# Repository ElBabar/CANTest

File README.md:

# CANTest

A board designed to test CAN connectivity between 2 arduino nanos

The CAN bus is made using mcp2551 and mcp2515.

LEDs were placed to monitor SPI and CAN activity for debug purposes. A new, cleaner version is being designed (see TXDemo).

This designed was intended simple on a single faced PCB in order to produce it with tools I had under hand.

You might need to use my library:
add https://github.com/ElBabar/Libabar.git
to your KiCad paths.

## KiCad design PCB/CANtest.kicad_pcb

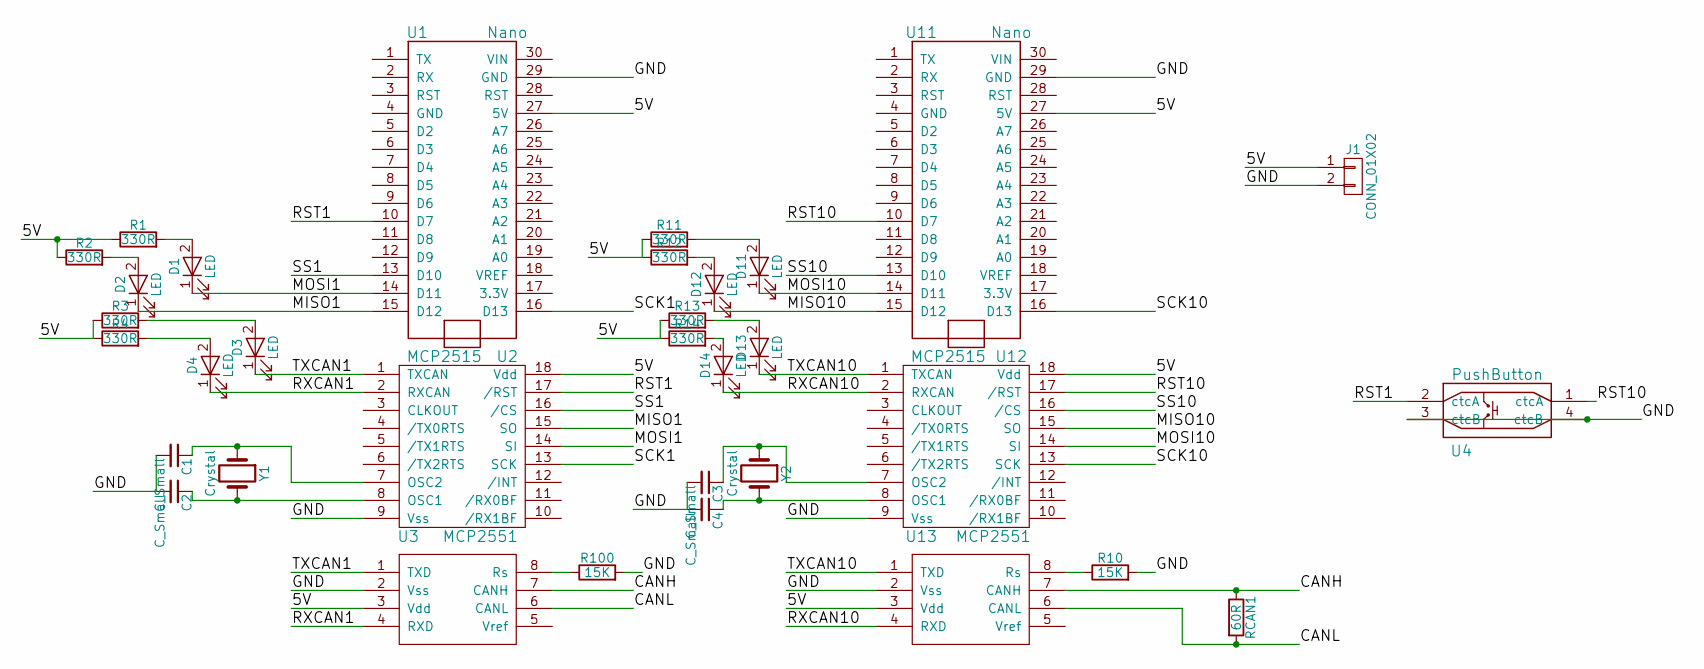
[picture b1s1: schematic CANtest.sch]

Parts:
C1, C2, C3, C4: C_Small; C_Disc_D3.0mm_W1.6mm_P2.50mm
D1, D2, D3, D4, D11, D12, D13, D14: LED; LED_D5.0mm
J1: CONN_01X02; Molex_KK-6410-02_02x2.54mm_Straight
R1, R2, R3, R4, R11, R12, R13, R14: 330R; R_Axial_DIN0207_L6.3mm_D2.5mm_P7.62mm_Horizontal
R10, R100: 15K; R_Axial_DIN0207_L6.3mm_D2.5mm_P10.16mm_Horizontal
RCAN1: 60R; R_Axial_DIN0207_L6.3mm_D2.5mm_P10.16mm_Horizontal
U1, U11: Nano
U2, U12: MCP2515; DIP-18_W7.62mm
U3, U13: MCP2551; DIP-8_W7.62mm
U4: PushButton
Y1, Y2: Crystal; Resonator-2pin_w10.0mm_h5.0mm

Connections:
/5V: J1.1, R1.1, R2.1, R3.1, R4.1, R11.1, R12.1, R13.1, R14.1, U1.27 (5V), U2.18 (Vdd), U3.3 (Vdd), U11.27 (5V), U12.18 (Vdd), U13.3 (Vdd)
/CANH: RCAN1.1, U3.7 (CANH), U13.7 (CANH)
/CANL: RCAN1.2, U3.6 (CANL), U13.6 (CANL)
/GND: C1.2, C2.2, C3.2, C4.2, J1.2, R10.2, R100.2, U1.29 (GND), U2.9 (Vss), U3.2 (Vss), U4.3 (ctcB), U4.4 (ctcB), U11.29 (GND), U12.9 (Vss), U13.2 (Vss)
/MISO1: D2.1 (K), U1.15 (D12), U2.15 (SO)
/MISO10: D12.1 (K), U11.15 (D12), U12.15 (SO)
/MOSI1: D1.1 (K), U1.14 (D11), U2.14 (SI)
/MOSI10: D11.1 (K), U11.14 (D11), U12.14 (SI)
/RST1: U1.10 (D7), U2.17 (/RST), U4.2 (ctcA)
/RST10: U4.1 (ctcA), U11.10 (D7), U12.17 (/RST)
/RXCAN1: D4.1 (K), U2.2 (RXCAN), U3.4 (RXD)
/RXCAN10: D14.1 (K), U12.2 (RXCAN), U13.4 (RXD)
/SCK1: U1.16 (D13), U2.13 (SCK)
/SCK10: U11.16 (D13), U12.13 (SCK)
/SS1: U1.13 (D10), U2.16 (/CS)
/SS10: U11.13 (D10), U12.16 (/CS)
/TXCAN1: D3.1 (K), U2.1 (TXCAN), U3.1 (TXD)
/TXCAN10: D13.1 (K), U12.1 (TXCAN), U13.1 (TXD)
unnamed: C1.1, U2.7 (OSC2), Y1.1
unnamed: C2.1, U2.8 (OSC1), Y1.2
unnamed: C3.1, U12.7 (OSC2), Y2.1
unnamed: C4.1, U12.8 (OSC1), Y2.2
unnamed: D1.2 (A), R1.2
unnamed: D2.2 (A), R2.2
unnamed: D3.2 (A), R3.2
unnamed: D4.2 (A), R4.2
unnamed: D11.2 (A), R11.2
unnamed: D12.2 (A), R12.2
unnamed: D13.2 (A), R13.2
unnamed: D14.2 (A), R14.2
unnamed: R10.1, U13.8 (Rs)
unnamed: R100.1, U3.8 (Rs)

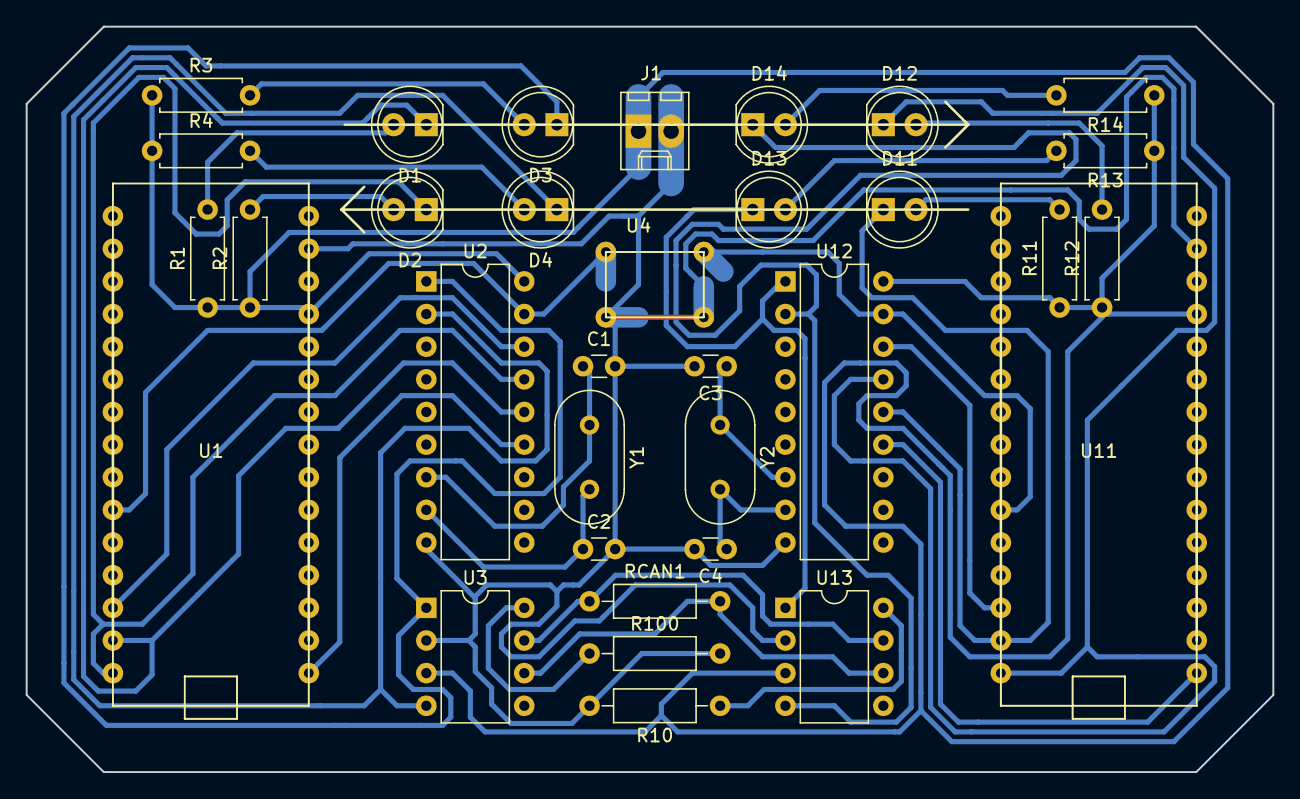
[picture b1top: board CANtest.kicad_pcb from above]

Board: 2 copper layers, 97.0 x 58.0 mm, 33 parts (0 on the bottom side), 32 nets.

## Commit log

2017-12-08 Changed tree
2017-12-08 Moved Readme
